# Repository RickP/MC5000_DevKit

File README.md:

# MC5000_DevKit

A development board that brings the [Shenzhen IO game](https://www.zachtronics.com/shenzhen-io/) to real hardware.

This documentation is intended for people who want to build/extend/bugfix the hardware. 

If you have an MC5000 DevKit board and want to play with it go to the [user documentation](https://rickp.github.io/MC5000_DevKit/).

**I'm planning to order some ready-to-use boards if there are enough people interested. Drop me a message (pannen at gmail dot com) if you're interested in getting one or more**

## Overview

The project consists of three parts. The firmware for the PFS173 microcontroller used in this project, a circuit board that connects to a computer via USB and a cross-platform desktop application that is used to programm the board.

The main use of this is to teach beginners the basics of programming and electronics by solving problems with increasing difficulty. Users have to make electric connection on the circuit board with jumper cable and programm the two microcontrollers with a simplified assembler language to solve the tasks.

## The circuit board

The board is designed in KiCAD 5, an OpenSource electronics CAD package. In the spirit of the game it is made with the cheapest components I could find. 

The design files are contained in the subfolder 'pcb'. The production files that are needed to make completely assembled boards (Gerbers, Pick&Place, BOM) are compiled automatically and can be found on the [releases page](https://github.com/RickP/MC5000_DevKit/releases) in the zip package "PCB_fabrication_files_for_jlcpcb.zip". 

Currently everything optimized for the chinese board manufacturer [JLCPB](https://jlcpcb.com). Just upload the gerbers (2 layers, 1.6mm PCB), choose "SMT Assembly" and upload the BOM and Pick&Place file when asked for it. For some reason you can have green, black, red or blue boards if you order up to 30 boards. For 50 boards they have to be green or black. If you order 50 boards each one is under 7 Euros including shipping and taxes to the EU (with the 'EuroPackage' shipping option').

Please check if all components are mounted the right way around when ordering. I tried to make sure everything fits but I may not have ordered the latest iteration myself. Also it would be nice it you give me some feedback if you order these. E.g. mention me in a tweet about it (@r1ckp).

## Microcontroller Firmware

The board uses 4 Padauk PFS173 microcontrollers. These are super cheap chinese 8bit microcontrollers that cost about 8cent per piece. They have 3 kilowords of flash ROM and 256 bytes of RAM.

The firmware for the two application controllers (a.k.a. MC5000) and the buzzer and display controller are in the subfolder 'firmware'. They are made with the [Free PDK toolchain](https://free-pdk.github.io) an open-source toolchain for many of the Padauk microcontrollers. It uses the SDCC compiler suite.

The code structure may look a bit weird at first but I had to made some strange constructions to trick the compiler into using as little memory as possible as I was constantly running out of it. **Make sure you use the version 4.1.0 of SDCC as it otimizes the code for the Padauk ICs much better than the 4.0.0 release.**

In order to flash the ICs you have to make or buy an Easy PDK programmer. The programmer is open hardware. I got mine assempled from amazon but you can make one yourself [production files](https://kitspace.org/boards/github.com/free-pdk/easy-pdk-programmer-hardware/). If you want to flash the firmware you need the programmer and the [easy-pdk-programmer software](https://github.com/free-pdk/easy-pdk-programmer-software). 

With the SDCC compiler and easypdkprog in your path just place the breakout boards on the programmer and execute the makefiles:

    cd firmware/MCU5000
    make flash1       # Flash MCU1
    make flash2       # Flash MCU2
    cd ../BUZZER
    make flash        # Flash Buzzer
    cd ../DISPLAY
    make flash        # Flash Display

Firmware binaries can be found on the [releases page](https://github.com/RickP/MC5000_DevKit/releases).

For binary flashing the two MCU5000 ICs have to be flashed with different CPU-IDs:

MCU1: `easypdkprog -s 31 -n PFS173 write MC5000.PFS173.ihx`

MCU2: `easypdkprog -s 32 -n PFS173 write MC5000.PFS173.ihx`

The two peripheral controllers are just flashed without a cpu id:

BUZZER: `easypdkprog -n PFS173 write buzzer.PFS173.ihx`

DISPLAY: `easypdkprog -n PFS173 write display.PFS173.ihx`

## Desktop application

The desktop application parses the code to a binary format and uploads it to the virtual 'MC5000' controllers on the board. It's written in QT5 (Version 5.12.8) and compiled automatically into packages for Linux, MacOS and Windows. Installation instructions are part of the [user documentation](https://rickp.github.io/MC5000_DevKit/).

The code is very simplistic with a lot of room for improvents. It's contained within the 'gui' subdirectory. The binaries can be found on the [releases page](https://github.com/RickP/MC5000_DevKit/releases).

**Currently there's a bug that prevents the rudimantary code error checking for MCU2!**

## Github actions

The releases including binary packages for four platforms and PCB fabrication files are created by a github action (see ".github/workflows/main.yml"). It also signs the MacOS app with my certificate that is stored in github secrets. The built is triggered when the repository is tagged.

If you want the same functionality for the MacOS package on your own fork fork you have to add some secrets in "Project settings/Secrets/Repository secrets":

- APPLE_DEV_USER: Your apple development account user name
- APPLE_DEV_PASS: An application specific password for your apple dev account
- APPLE_DEV_CERT: Your exported developer certificate (including private key) in base64 encoding. Use the same application specific password as above for the cert.

If you don't have an apple developer password you can also remove the signing part from the action. Be aware that this will make the installation of the app for MacOS users much less nice because they will get warnings and have to explicitly allow the execution in the security settings.

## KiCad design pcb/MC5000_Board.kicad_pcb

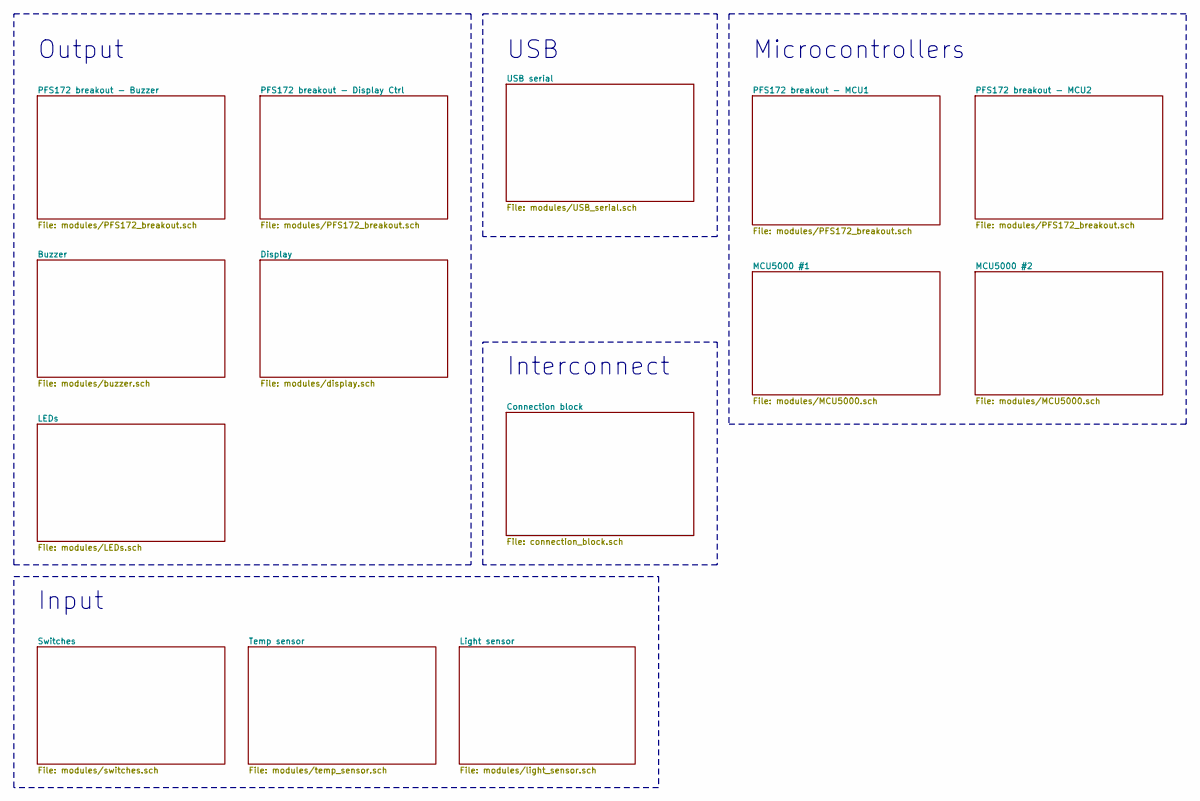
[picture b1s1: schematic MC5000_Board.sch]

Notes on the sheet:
Microcontrollers
Interconnect
USB
Output
Input

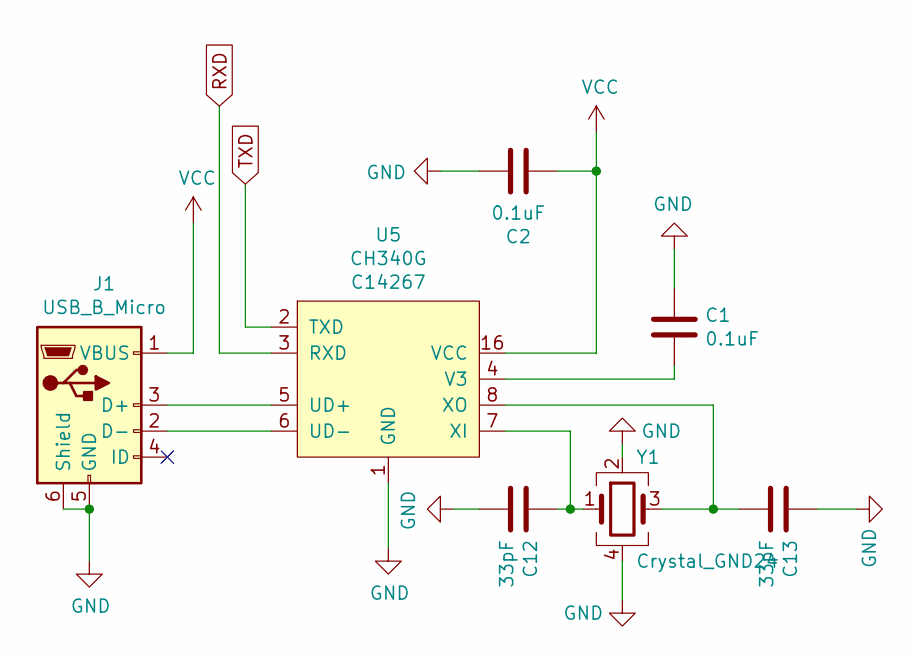
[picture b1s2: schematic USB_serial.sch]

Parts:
C1, C2: 0.1uF; C_0603_1608Metric_Pad1.08x0.95mm_HandSolder; LCSC C14663
C12, C13: 33pF; C_0603_1608Metric_Pad1.08x0.95mm_HandSolder; LCSC C1663
J1: USB_B_Micro; MicroXNJ; LCSC C404969
U5: CH340G; SOP-16_3.9x9.9mm_P1.27mm_rotated; LCSC C14267
Y1: Crystal_GND24; Crystal_SMD_3225-4Pin_3.2x2.5mm; LCSC C9002

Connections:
GND: C1.1, C2.1, C12.2, C13.1, J1.5 (GND), J1.6 (Shield), U5.1 (GND), Y1.2, Y1.4; also elsewhere on the board
unnamed: C1.2, U5.4 (V3)
unnamed: C12.1, U5.7 (XI), Y1.1
unnamed: C13.2, U5.8 (XO), Y1.3
unnamed: J1.2 (D-), U5.6 (UD-)
unnamed: J1.3 (D+), U5.5 (UD+)
RXD: U5.3 (RXD); also elsewhere on the board
TXD: U5.2 (TXD); also elsewhere on the board
VCC: C2.2, J1.1 (VBUS), U5.16 (VCC); also elsewhere on the board

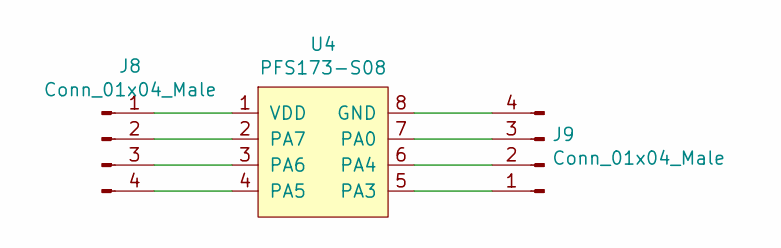
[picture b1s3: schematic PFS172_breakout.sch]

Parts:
J2, J3: Conn_01x04_Male; PinHeader_1x04_P2.54mm_plug; LCSC C124378
U1: PFS173-S08; SOP-8_3.9x4.9mm_P1.27mm_rotated; LCSC C337970

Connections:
unnamed: J2.1, U1.1 (VDD)
unnamed: J2.2, U1.2 (PA7)
unnamed: J2.3, U1.3 (PA6)
unnamed: J2.4, U1.4 (PA5)
unnamed: J3.1, U1.5 (PA3)
unnamed: J3.2, U1.6 (PA4)
unnamed: J3.3, U1.7 (PA0)
unnamed: J3.4, U1.8 (GND)

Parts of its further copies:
J4, J5, J6, J7, J8, J9, J10, J11, J12, J13: Conn_01x04_Male; PinHeader_1x04_P2.54mm_plug; LCSC C124378
U2, U3, U4, U6, U7: PFS173-S08; SOP-8_3.9x4.9mm_P1.27mm_rotated; LCSC C337970

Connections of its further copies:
unnamed: J4.1, U2.1 (VDD)
unnamed: J4.2, U2.2 (PA7)
unnamed: J4.3, U2.3 (PA6)
unnamed: J4.4, U2.4 (PA5)
unnamed: J5.1, U2.5 (PA3)
unnamed: J5.2, U2.6 (PA4)
unnamed: J5.3, U2.7 (PA0)
unnamed: J5.4, U2.8 (GND)
unnamed: J6.1, U3.1 (VDD)
unnamed: J6.2, U3.2 (PA7)
unnamed: J6.3, U3.3 (PA6)
unnamed: J6.4, U3.4 (PA5)
unnamed: J7.1, U3.5 (PA3)
unnamed: J7.2, U3.6 (PA4)
unnamed: J7.3, U3.7 (PA0)
unnamed: J7.4, U3.8 (GND)
unnamed: J8.1, U4.1 (VDD)
unnamed: J8.2, U4.2 (PA7)
unnamed: J8.3, U4.3 (PA6)
unnamed: J8.4, U4.4 (PA5)
unnamed: J9.1, U4.5 (PA3)
unnamed: J9.2, U4.6 (PA4)
unnamed: J9.3, U4.7 (PA0)
unnamed: J9.4, U4.8 (GND)

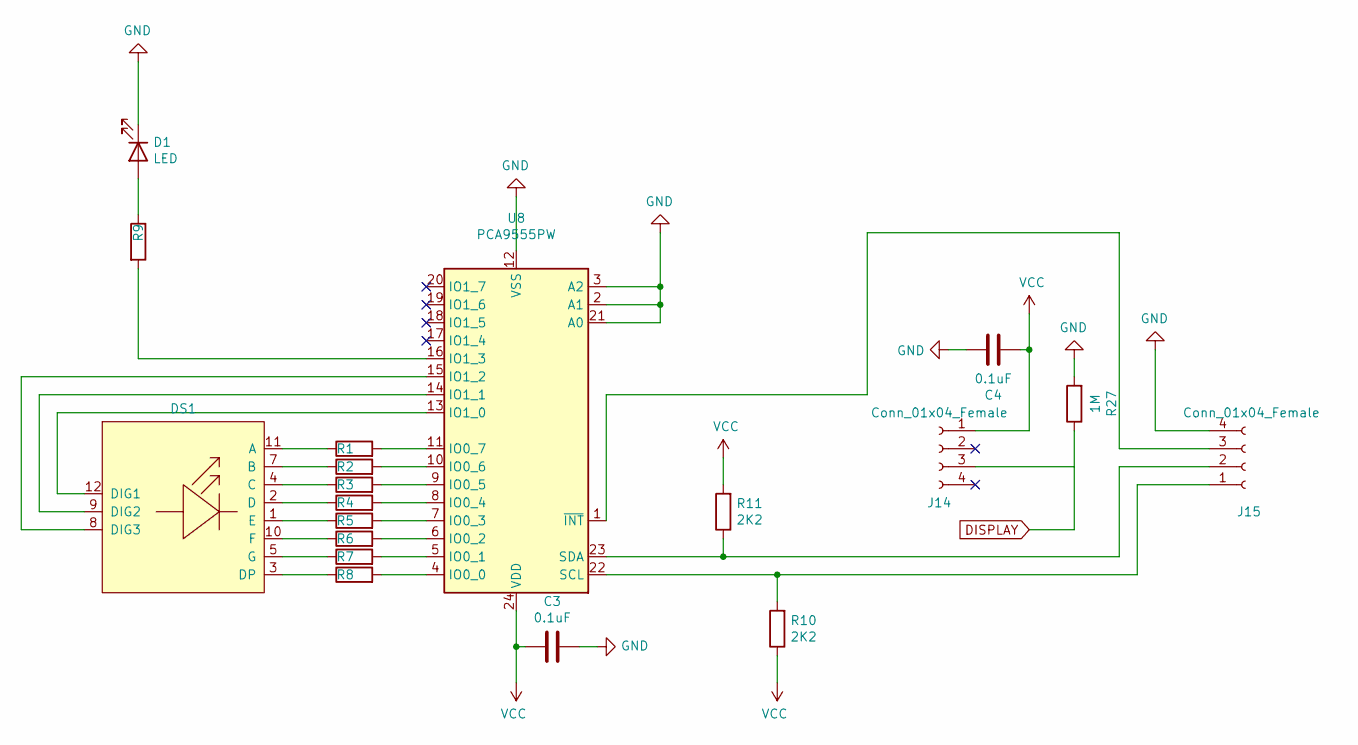
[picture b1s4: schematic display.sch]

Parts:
C3, C4: 0.1uF; C_0603_1608Metric_Pad1.08x0.95mm_HandSolder; LCSC C14663
D1: LED; LED_0805_2012Metric_Pad1.15x1.40mm_HandSolder; LCSC C2297
DS1: SLR0523DYA1BD; LCSC C225932
J14, J15: Conn_01x04_Female; PinHeader_1x04_P2.54mm_Vertical_centered; LCSC C124378
R1, R2, R3, R4, R5, R6, R7, R8: 220R; R_0603_1608Metric_Pad0.98x0.95mm_HandSolder; LCSC C22962
R9, R10, R11: 2K2; R_0603_1608Metric_Pad0.98x0.95mm_HandSolder; LCSC C4190
R27: 1M; R_0603_1608Metric_Pad0.98x0.95mm_HandSolder; LCSC C22935
U8: PCA9555PW; TSSOP-24_4.4x7.8mm_P0.65mm_rotated; LCSC C128392

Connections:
DISPLAY: J14.3, R27.1; also elsewhere on the board
GND: C3.1, C4.1, D1.1 (K), J15.4, R27.2, U8.2 (A1), U8.3 (A2), U8.12 (VSS), U8.21 (A0); also elsewhere on the board
unnamed: D1.2 (A), R9.1
unnamed: DS1.1 (E), R5.1
unnamed: DS1.2 (D), R4.1
unnamed: DS1.3 (DP), R8.1
unnamed: DS1.4 (C), R3.1
unnamed: DS1.5 (G), R7.1
unnamed: DS1.7 (B), R2.1
unnamed: DS1.8 (DIG3), U8.15 (IO1_2)
unnamed: DS1.9 (DIG2), U8.14 (IO1_1)
unnamed: DS1.10 (F), R6.1
unnamed: DS1.11 (A), R1.1
unnamed: DS1.12 (DIG1), U8.13 (IO1_0)
unnamed: J15.1, R10.2, U8.22 (SCL)
unnamed: J15.2, R11.1, U8.23 (SDA)
unnamed 69: J15.3, U8.1 (~INT); also elsewhere on the board
unnamed: R1.2, U8.11 (IO0_7)
unnamed: R2.2, U8.10 (IO0_6)
unnamed: R3.2, U8.9 (IO0_5)
unnamed: R4.2, U8.8 (IO0_4)
unnamed: R5.2, U8.7 (IO0_3)
unnamed: R6.2, U8.6 (IO0_2)
unnamed: R7.2, U8.5 (IO0_1)
unnamed: R8.2, U8.4 (IO0_0)
unnamed: R9.2, U8.16 (IO1_3)
VCC: C3.2, C4.2, J14.1, R10.1, R11.2, U8.24 (VDD); also elsewhere on the board

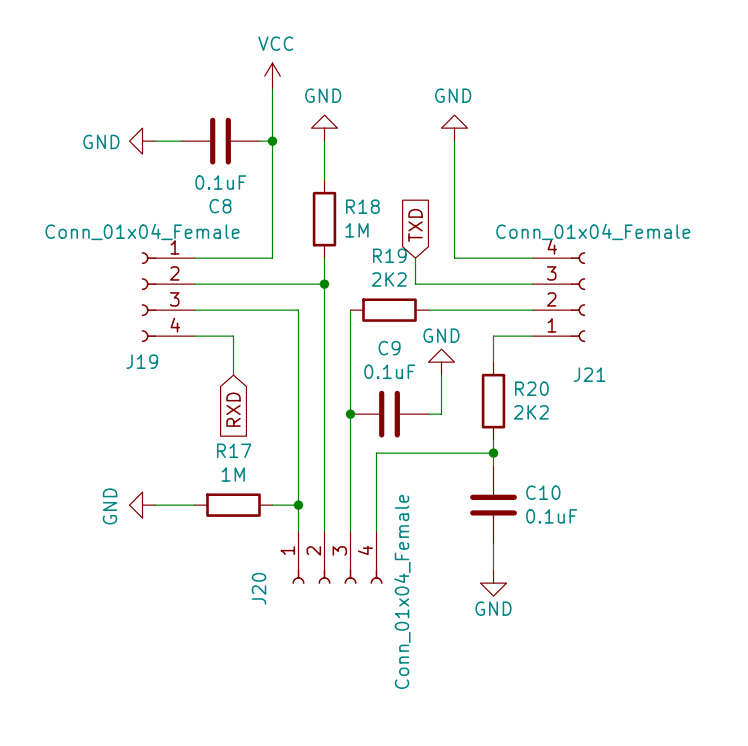
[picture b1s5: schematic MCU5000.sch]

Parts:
C5, C6, C7: 0.1uF; C_0603_1608Metric_Pad1.08x0.95mm_HandSolder; LCSC C14663
J16, J18: Conn_01x04_Female; PinHeader_1x04_P2.54mm_Vertical_centered; LCSC C124378
J17: Conn_01x04_Female; PinSocket_1x04_P2.54mm_Vertical_centered; LCSC C124413
R13, R14: 1M; R_0603_1608Metric_Pad0.98x0.95mm_HandSolder; LCSC C22935
R15, R16: 2K2; R_0603_1608Metric_Pad0.98x0.95mm_HandSolder; LCSC C4190

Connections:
GND: C5.1, C6.1, C7.1, J18.4, R13.2, R14.1; also elsewhere on the board
unnamed: C6.2, J17.3, R15.2
unnamed: C7.2, J17.4, R16.1
unnamed: J16.2, J17.2, R14.2
unnamed: J16.3, J17.1, R13.1
unnamed: J18.1, R16.2
unnamed: J18.2, R15.1
RXD: J16.4; also elsewhere on the board
TXD: J18.3; also elsewhere on the board
VCC: C5.2, J16.1; also elsewhere on the board

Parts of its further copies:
C8, C9, C10: 0.1uF; C_0603_1608Metric_Pad1.08x0.95mm_HandSolder; LCSC C14663
J19, J21: Conn_01x04_Female; PinHeader_1x04_P2.54mm_Vertical_centered; LCSC C124378
J20: Conn_01x04_Female; PinSocket_1x04_P2.54mm_Vertical_centered; LCSC C124413
R17, R18: 1M; R_0603_1608Metric_Pad0.98x0.95mm_HandSolder; LCSC C22935
R19, R20: 2K2; R_0603_1608Metric_Pad0.98x0.95mm_HandSolder; LCSC C4190

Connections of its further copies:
GND: C8.1, C9.1, C10.1, J21.4, R17.2, R18.1; also elsewhere on the board
unnamed: C9.2, J20.3, R19.2
unnamed: C10.2, J20.4, R20.1
unnamed: J19.2, J20.2, R18.2
unnamed: J19.3, J20.1, R17.1
unnamed: J21.1, R20.2
unnamed: J21.2, R19.1
RXD: J19.4; also elsewhere on the board
TXD: J21.3; also elsewhere on the board
VCC: C8.2, J19.1; also elsewhere on the board

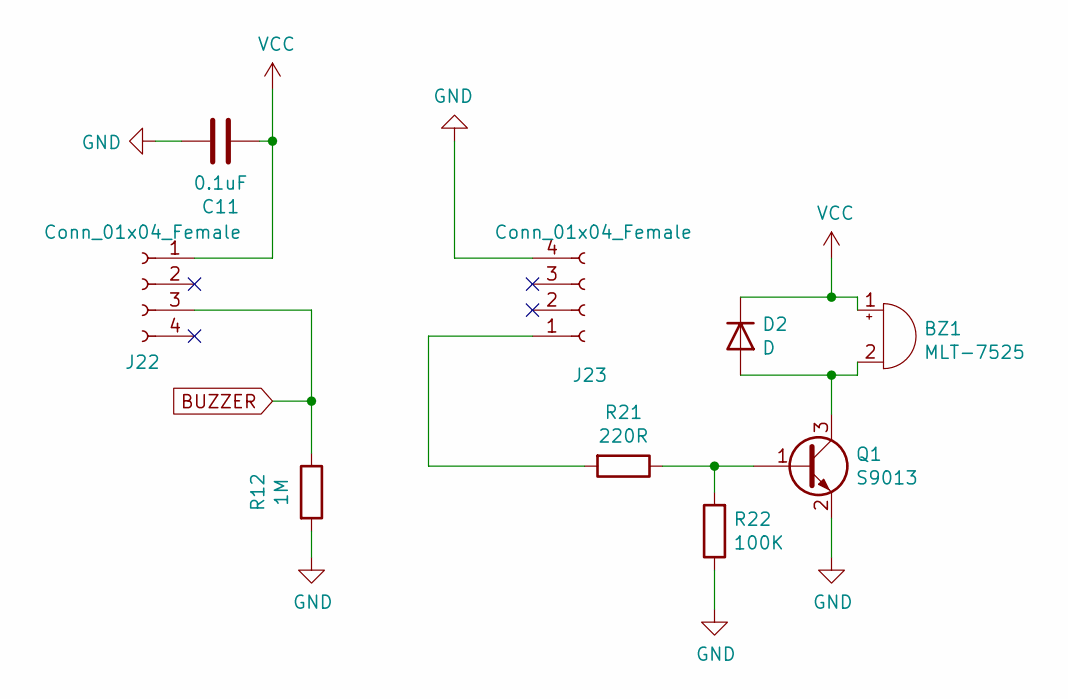
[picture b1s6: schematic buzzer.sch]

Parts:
BZ1: MLT-7525; MagneticBuzzer_7.5x7.5_SMT; LCSC C95299
C11: 0.1uF; C_0603_1608Metric_Pad1.08x0.95mm_HandSolder; LCSC C14663
D2: D; D_SOD-123F; LCSC C64898
J22, J23: Conn_01x04_Female; PinHeader_1x04_P2.54mm_Vertical_centered; LCSC C124378
Q1: S9013; SOT-23_rotated; LCSC C6749
R12: 1M; R_0603_1608Metric_Pad0.98x0.95mm_HandSolder; LCSC C22935
R21: 220R; R_0603_1608Metric_Pad0.98x0.95mm_HandSolder; LCSC C22962
R22: 100K; R_0603_1608Metric_Pad0.98x0.95mm_HandSolder; LCSC C25803

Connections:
BUZZER: J22.3, R12.1; also elsewhere on the board
GND: C11.1, J23.4, Q1.2 (E), R12.2, R22.1; also elsewhere on the board
unnamed: BZ1.2 (+), D2.2 (A), Q1.3 (C)
unnamed: J23.1, R21.2
unnamed: Q1.1 (B), R21.1, R22.2
VCC: BZ1.1 (-), C11.2, D2.1 (K), J22.1; also elsewhere on the board

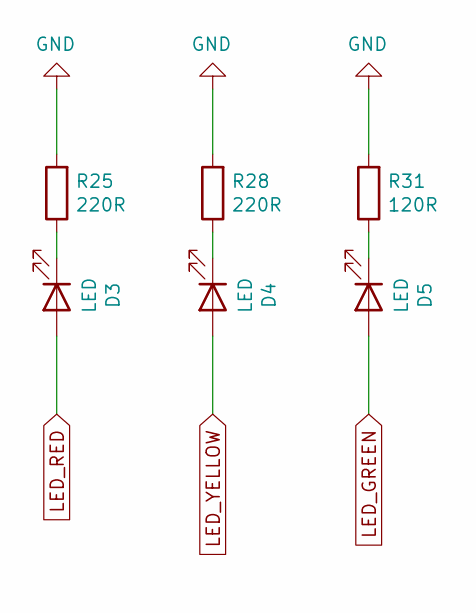
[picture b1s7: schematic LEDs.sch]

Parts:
D3: LED; LED_0805_2012Metric_Pad1.15x1.40mm_HandSolder; LCSC C84256
D4: LED; LED_0805_2012Metric_Pad1.15x1.40mm_HandSolder; LCSC C2296
D5: LED; LED_0805_2012Metric_Pad1.15x1.40mm_HandSolder; LCSC C2297
R25, R28: 220R; R_0603_1608Metric_Pad0.98x0.95mm_HandSolder; LCSC C22962
R31: 120R; R_0603_1608Metric_Pad0.98x0.95mm_HandSolder; LCSC C22787

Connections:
GND: R25.2, R28.2, R31.2; also elsewhere on the board
LED_GREEN: D5.2 (A); also elsewhere on the board
LED_RED: D3.2 (A); also elsewhere on the board
LED_YELLOW: D4.2 (A); also elsewhere on the board
unnamed: D3.1 (K), R25.1
unnamed: D4.1 (K), R28.1
unnamed: D5.1 (K), R31.1

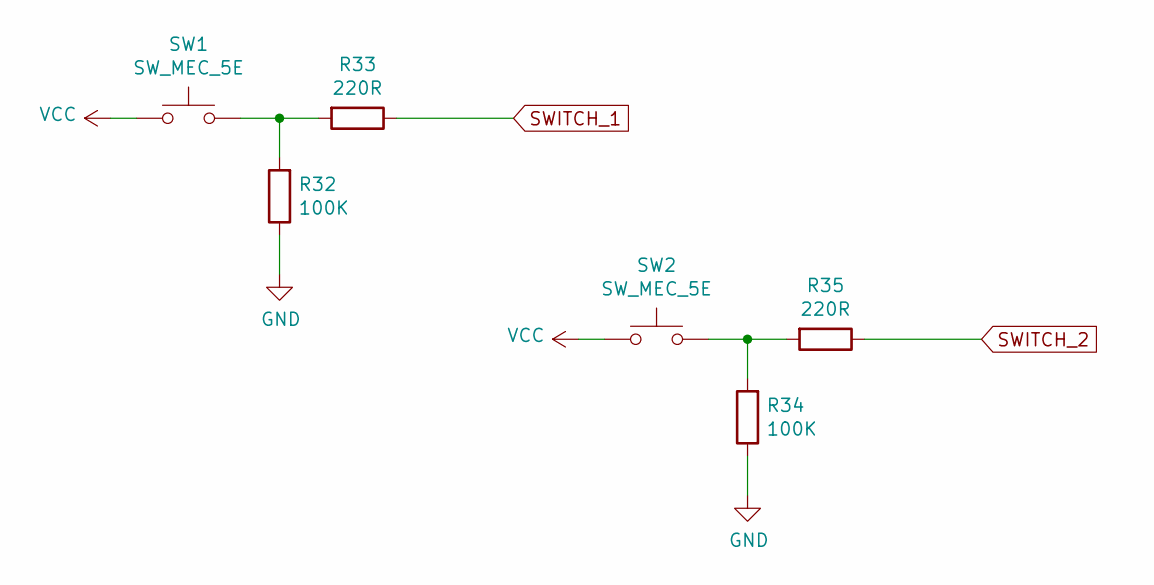
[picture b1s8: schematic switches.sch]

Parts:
R32, R34: 100K; R_0603_1608Metric_Pad0.98x0.95mm_HandSolder; LCSC C25803
R33, R35: 220R; R_0603_1608Metric_Pad0.98x0.95mm_HandSolder; LCSC C22962
SW1, SW2: SW_MEC_5E; SW_Push_1P1T_NO_CK_KSC6xxJ; LCSC C318889

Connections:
GND: R32.1, R34.1; also elsewhere on the board
unnamed: R32.2, R33.2, SW1.2
unnamed: R34.2, R35.2, SW2.2
SWITCH_1: R33.1; also elsewhere on the board
SWITCH_2: R35.1; also elsewhere on the board
VCC: SW1.1, SW2.1; also elsewhere on the board

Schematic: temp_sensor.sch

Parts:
R23: 100K; R_0603_1608Metric_Pad0.98x0.95mm_HandSolder; LCSC C25803
R24: NTC - 100k; R_0603_1608Metric_Pad0.98x0.95mm_HandSolder; LCSC C92368

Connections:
GND: R23.2; also elsewhere on the board
TEMP_SENSOR: R23.1, R24.2; also elsewhere on the board
VCC: R24.1; also elsewhere on the board

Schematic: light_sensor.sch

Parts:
D6: SMD3528C-50; LED_1210_3225Metric_Pad1.42x2.65mm_rotated; LCSC C242256
R26: 10K; R_0603_1608Metric_Pad0.98x0.95mm_HandSolder; LCSC C25804

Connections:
GND: R26.1; also elsewhere on the board
LIGHT_SENSOR: D6.1, R26.2; also elsewhere on the board
VCC: D6.2; also elsewhere on the board

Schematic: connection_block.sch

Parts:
J24: Conn_01x04_Female; PinSocket_1x04_P2.54mm_Vertical_centered; LCSC C124413
J25: Conn_01x05_Female; PinSocket_1x05_P2.54mm_Vertical_centered; LCSC C718240

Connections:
BUZZER: J25.2; also elsewhere on the board
DISPLAY: J25.1; also elsewhere on the board
LED_GREEN: J25.5; also elsewhere on the board
LED_RED: J25.3; also elsewhere on the board
LED_YELLOW: J25.4; also elsewhere on the board
LIGHT_SENSOR: J24.4; also elsewhere on the board
SWITCH_1: J24.1; also elsewhere on the board
SWITCH_2: J24.2; also elsewhere on the board
TEMP_SENSOR: J24.3; also elsewhere on the board

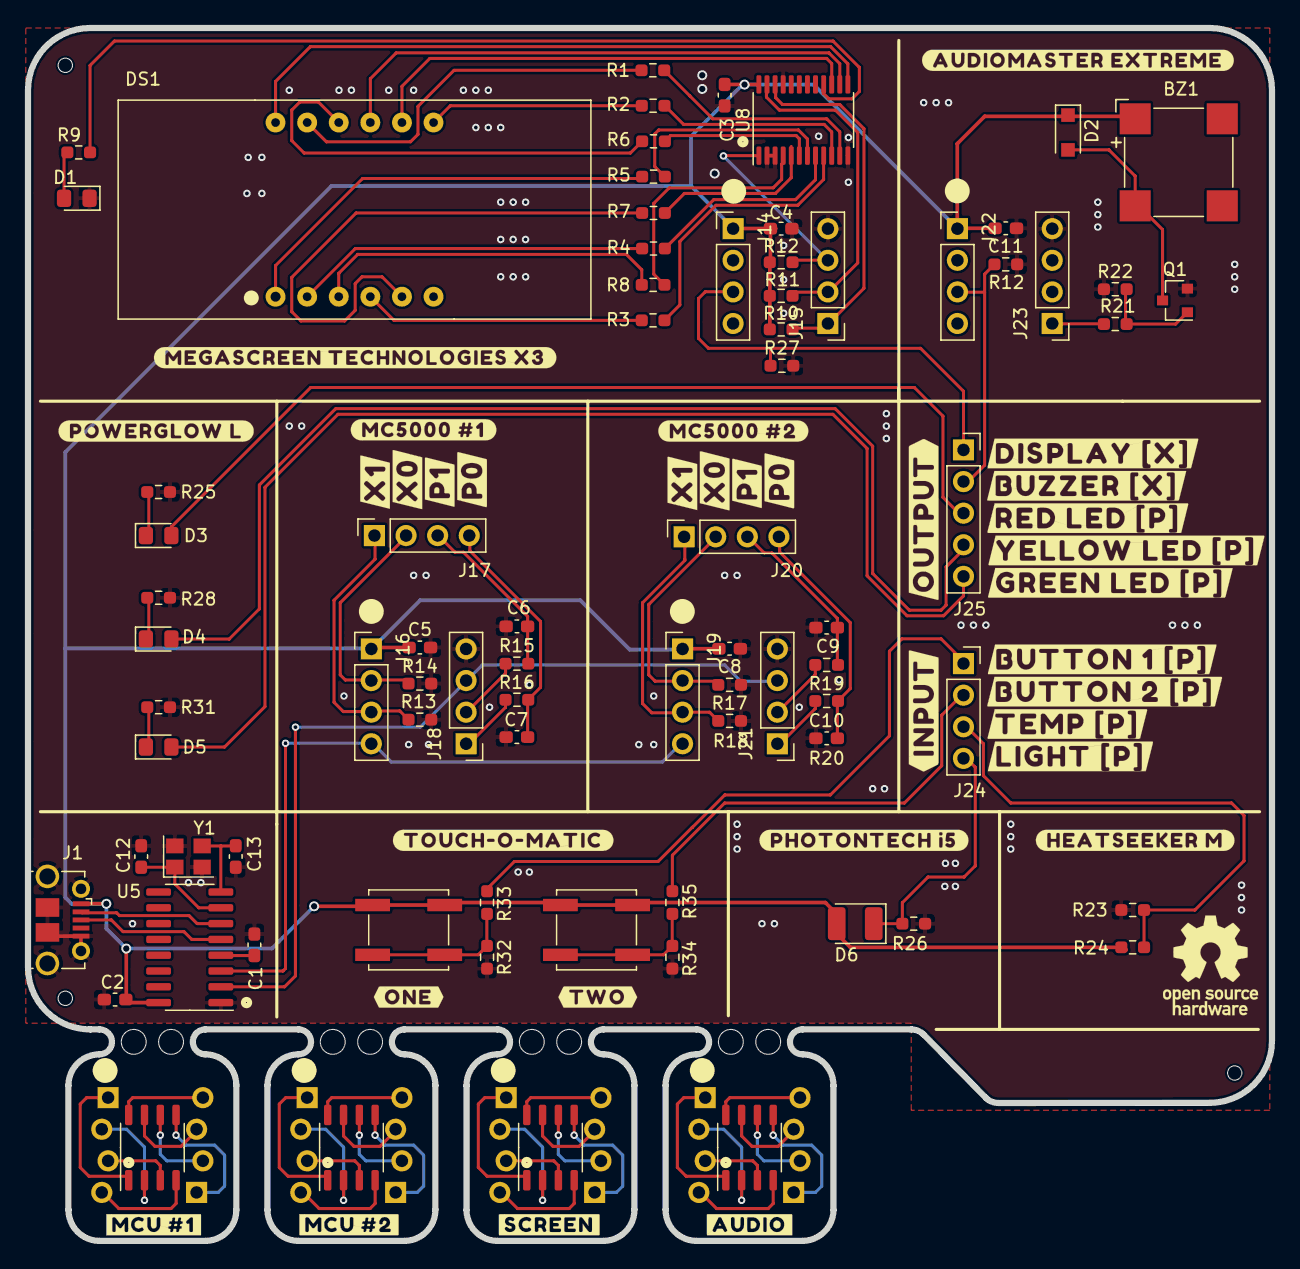
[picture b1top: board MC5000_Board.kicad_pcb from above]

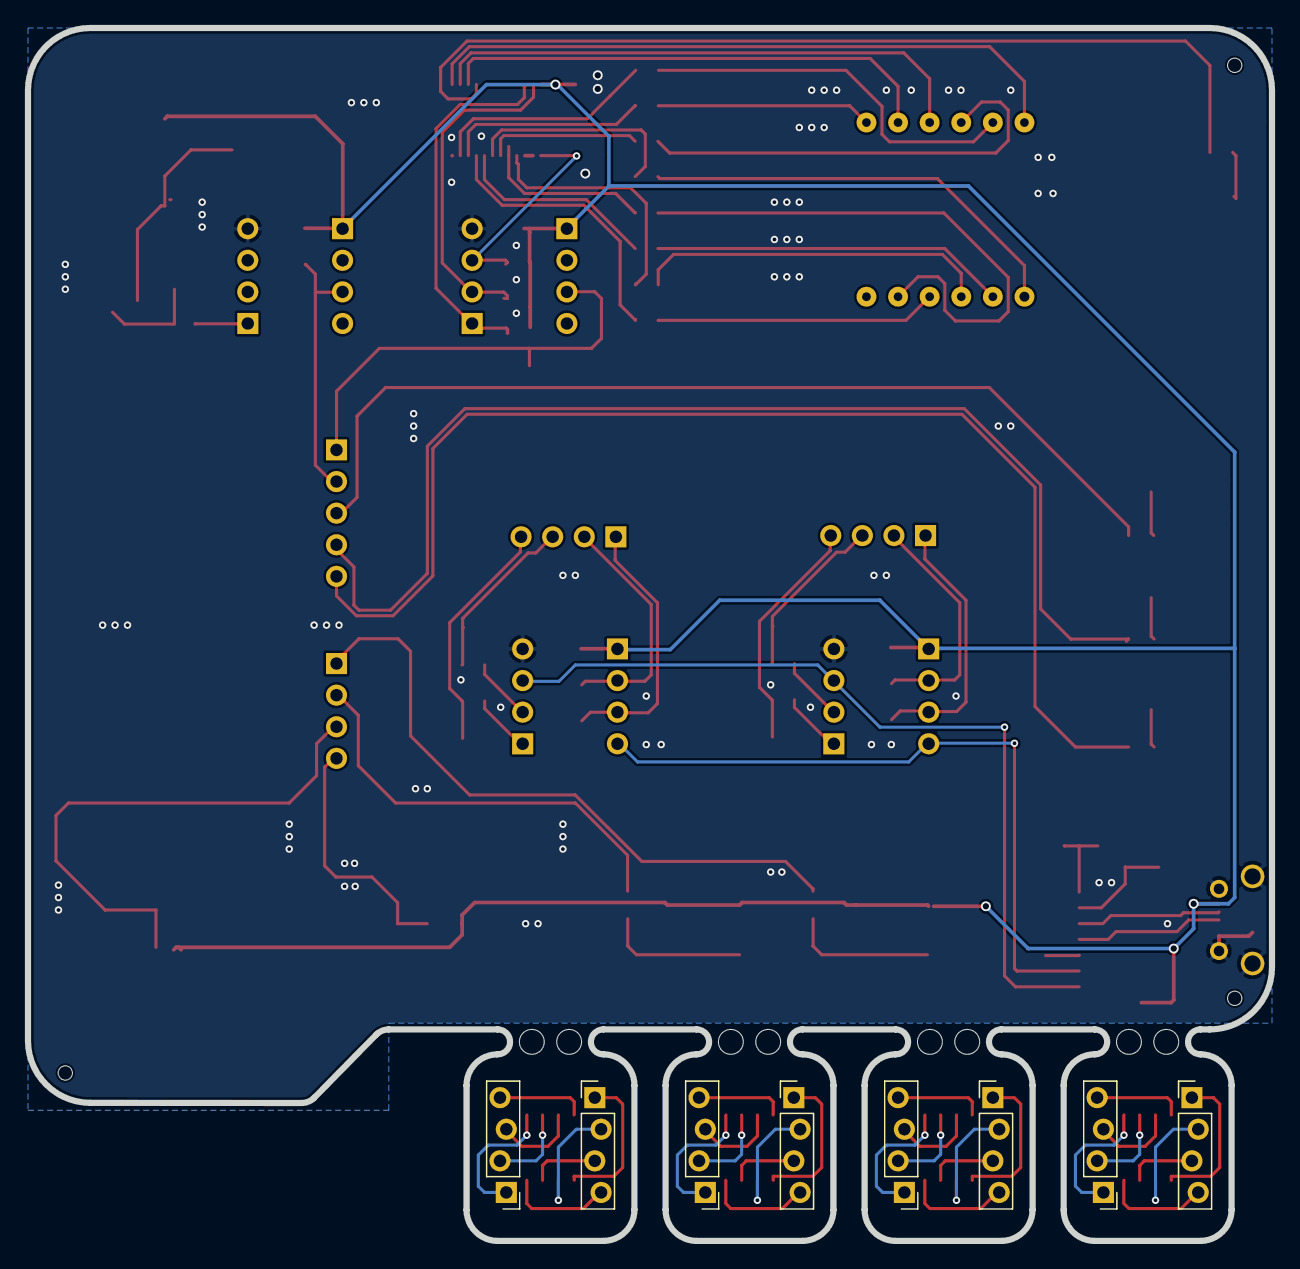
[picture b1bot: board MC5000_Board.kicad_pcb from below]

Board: 2 copper layers, 100.0 x 97.5 mm, 86 parts (8 on the bottom side), 94 nets.

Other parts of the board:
R12#2: 100K; R_0603_1608Metric_Pad0.98x0.95mm_HandSolder

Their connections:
unnamed 69: R12#2.1; also elsewhere on the board
VCC: R12#2.2; also elsewhere on the board

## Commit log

2021-01-21 init
2021-01-22 Sleep cmd implemented
2021-01-22 added gui, restructured repo
2021-01-26 Bugfixes
2021-01-27 gui register display
2021-01-28 Down to 2400 baud
2021-01-28 Cleaned up gui command code
2021-01-28 memory optimizations
2021-01-29 cleanup + 19200 baud
2021-02-01 Fixed jmp and labels
2021-02-01 xbus work
2021-02-01 more xbus (still sucks)
2021-02-02 Freed up some memory in strange ways
2021-02-02 Rumgefrickel
2021-02-02 More desperate measures to save memory
2021-02-03 added dst and dgd commands
2021-02-05 changed back code length
2021-02-09 QT gui
2021-02-09 tuned gitignore
2021-02-09 gui work
2021-02-09 Added c++ serialport stuff
2021-02-09 Added serial connect button
2021-02-11 Added font
2021-02-11 Added error message to gui
2021-02-11 Serial encoding done
2021-02-12 Removed local files
2021-02-12 Not working ;(
2021-02-15 Changed gitignore
2021-02-15 Made it work!
2021-02-15 fixes
2021-02-16 Various fixes; added GUI icon
2021-02-17 Started implementing xbus
2021-02-17 Added readme
2021-02-17 build workflow
2021-02-17 F*ck XBUS!
2021-02-18 Made xbus0 work
2021-02-19 Feature complete!
2021-02-19 Added file save and load
2021-02-21 Added kicad gitignore
2021-02-21 Added pcb
2021-02-21 Make XBus work for other commands than mov
2021-02-22 various fixes
2021-02-23 sped up XBUS
2021-02-23 Sped up register aquirement; Cleanup
2021-02-23 Work on PCB
2021-02-23 tuned pwm frequency
2021-02-23 Tuned analog pins
2021-02-23 Nice labels
2021-02-24 Added buzzer
2021-02-24 Added LEDs
2021-02-25 Cleanup libs
2021-02-25 Added label for buzzer
2021-02-25 Added switches
2021-02-25 changed pcb file structure
2021-02-26 finished pcb
2021-02-26 Fixed 3D models
2021-02-26 Connected LEDs to GND
2021-03-02 Firmware cleanup; Limit lines and codesize in GUI
2021-03-02 shorter xbus time
2021-03-02 XBUS optimizations
2021-03-02 Serial optimizations
2021-03-03 More serial delay
2021-03-05 App rename
2021-03-05 Changed firmware directory structure
2021-03-05 Changed QTCreator config
2021-03-08 font sizes
2021-03-08 Longer serial wait interval
2021-03-08 Changed xbus pins
2021-03-10 XBus changes; PCB changes
2021-03-11 Production board
2021-03-11 Stuff
2021-03-11 imagebuilder
2021-03-11 Added mac image
    Former-commit-id: 7643f60ed158f56754359eba66d795ca97ca789e
2021-03-11 Added linux amd64 image
    Former-commit-id: b350005f530877a701288a810bb2b46236d8df36
2021-03-11 Added linux interl image
    Former-commit-id: 6aa92ac7a474a7601d4811fd705a869abda7944c
2021-03-11 added macos build script
    Former-commit-id: b5701d850057fd321c1c9d51d326035f9f55ae74
2021-03-11 added macos build script
    Former-commit-id: f04b217c95dba94b6b68f0d56c771e49fbc90254 [formerly b5701d850057fd321c1c9d51d326035f9f55ae74]
    Former-commit-id: 9059d3562fee673c98b385301d415bdec7a3a97d
2021-03-11 added images to gitignore
    Former-commit-id: 005d7555e39c2006a8acf8a489d7daad6d6f22fa
2021-03-11 deleted large files
    Former-commit-id: 136d85d95edf6effa1a7b626afa25b6fb9e619b4
2021-03-11 Removed fab files
2021-03-11 Fixed USB footprint
2021-03-12 async serial
2021-03-12 async
2021-03-13 Faster serial, hardcoded 2 mcus
2021-03-13 added board with breakouts
2021-03-13 One PCB to rule them all
2021-03-13 Fabrication stuff
2021-03-14 Footprint changes
2021-03-15 Changed USB<->Serial to CH340G
2021-03-15 Added NOCONNECTION flags
2021-03-16 memory optimization
2021-03-16 extended code lines by 2
2021-03-16 XBus improvements?
2021-03-16 Added link to manual
2021-03-16 changed github action
2021-03-17 Fixed github actions
2021-03-17 Added firmware github action
2021-03-17 Added arm deployment
2021-03-17 QT5.12 compatibility
2021-03-17 Multiarch linux build
2021-03-18 Removed unused import
2021-03-18 Made osx notarization work with QT5.12
2021-03-18 Only build tags with github actions
2021-03-18 Added macos test
2021-03-18 Added macos build
2021-03-18 Build on tag only
2021-03-18 Build fabrication files
2021-03-18 Changed connectors
2021-03-18 Added fab files to github actions
2021-03-18 Build on tagging
2021-03-18 Mac signing test
2021-03-18 Sign and notarize mac app (No stapling)
2021-03-19 Staple app on release publishing
2021-03-19 Staple app after notarization
2021-03-19 Added docs
2021-03-19 Set theme jekyll-theme-hacker
2021-03-19 Changed documentation URL
2021-03-19 Changed documentation
2021-03-21 check kicad and make docs on push
2021-03-21 Uodate pcd docs
2021-03-21 Design changes
2021-03-21 Changed doc settings
2021-03-21 Changed overview schematic
2021-03-21 Create PBB image
2021-03-21 Uodate pcb docs
2021-03-21 Fixed typo
2021-03-21 Update pcb docs
2021-03-22 Fixed label bug; added example
2021-03-26 Create LICENSE
2021-03-26 Added OSHW logo
2021-03-26 Modified silkscreen
2021-03-26 Upload fix
2021-03-26 changed workflows
2021-03-27 firmware fixes
2021-03-27 GUI fixes
2021-03-29 Added documentation
2021-03-30 trying to fix upload
2021-03-30 GUI debug code
2021-03-30 Fixed upload
2021-03-30 Added levels
2021-03-31 Modified level3
2021-03-31 Modified installation instructions
2021-03-31 Extended number of buzzer tones to 35
2021-04-01 Extended buzzer sound range
2021-04-06 code cleanup
2021-04-08 Changed display LED color
2021-04-08 Made plug footprint tighter
2021-04-08 Slower XBus speed
2021-04-15 Changed USB port footprint
